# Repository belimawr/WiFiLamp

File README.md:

WiFi Lamp
=========

This is a simple project that uses a ESP8266-01 and a 2-coil latching relay
to control a lamp (or any other load) over WiFi using a simple web page.

TODO
----
 - Add the schematic
 - Create a nice PCB
 - Improve the web page

Licence
-------
**GPLV3**

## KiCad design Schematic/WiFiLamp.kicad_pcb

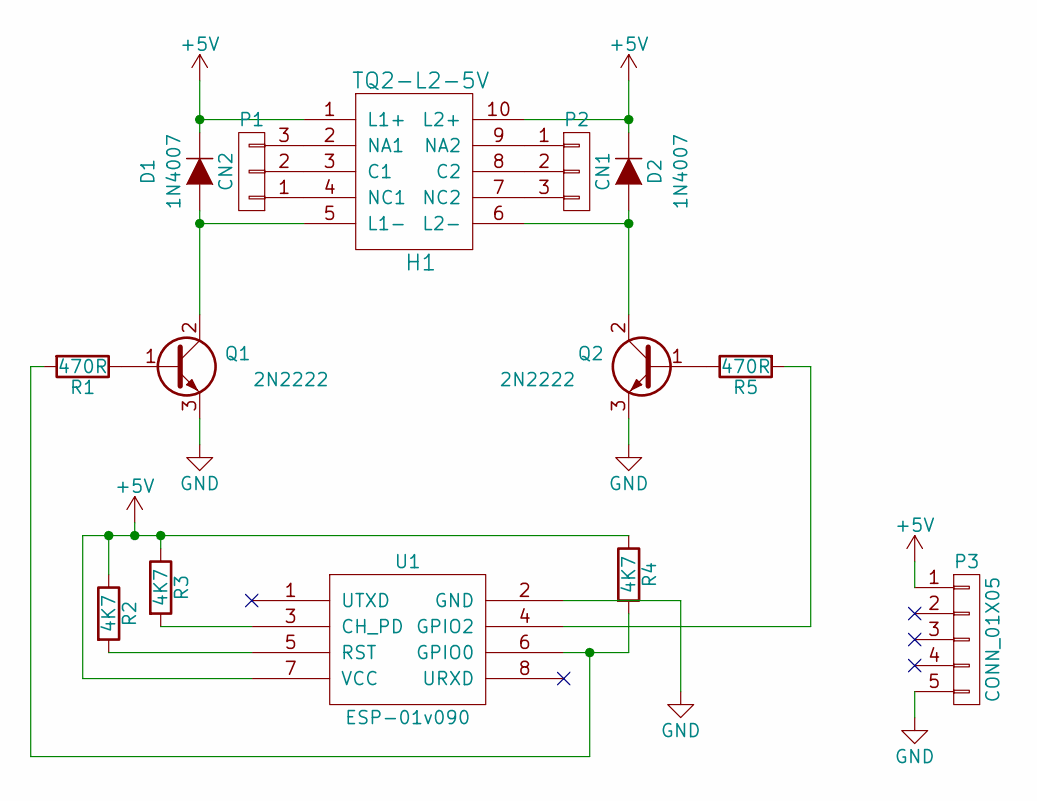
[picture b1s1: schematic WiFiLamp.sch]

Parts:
D1, D2: 1N4007; D_DO-41_SOD81_P10.16mm_Horizontal
H1: TQ2-L2-5V; ATQ229
P1: CN2; Pin_Header_Straight_1x03_Pitch2.54mm
P2: CN1; Pin_Header_Straight_1x03_Pitch2.54mm
P3: CONN_01X05; Pin_Header_Straight_1x05_Pitch2.54mm
Q1, Q2: 2N2222; TO-92_Inline_Narrow_Oval
R1, R5: 470R; R_Axial_DIN0207_L6.3mm_D2.5mm_P10.16mm_Horizontal
R2, R3, R4: 4K7; R_Axial_DIN0207_L6.3mm_D2.5mm_P10.16mm_Horizontal
U1: ESP-01v090; ESP-01

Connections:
+5V: D1.1 (K), D2.1 (K), H1.1 (L1+), H1.10 (L2+), P3.1, R2.1, R3.1, R4.1, U1.7 (VCC)
GND: P3.5, Q1.3 (E), Q2.3 (E), U1.2 (GND)
unnamed: D1.2 (A), H1.5 (L1-), Q1.2 (C)
unnamed: D2.2 (A), H1.6 (L2-), Q2.2 (C)
unnamed: H1.2 (NA1), P1.3
unnamed: H1.3 (C1), P1.2
unnamed: H1.4 (NC1), P1.1
unnamed: H1.7 (NC2), P2.3
unnamed: H1.8 (C2), P2.2
unnamed: H1.9 (NA2), P2.1
unnamed: Q1.1 (B), R1.1
unnamed: Q2.1 (B), R5.1
unnamed: R1.2, R4.2, U1.6 (GPIO0)
unnamed: R2.2, U1.5 (RST)
unnamed: R3.2, U1.3 (CH_PD)
unnamed: R5.2, U1.4 (GPIO2)

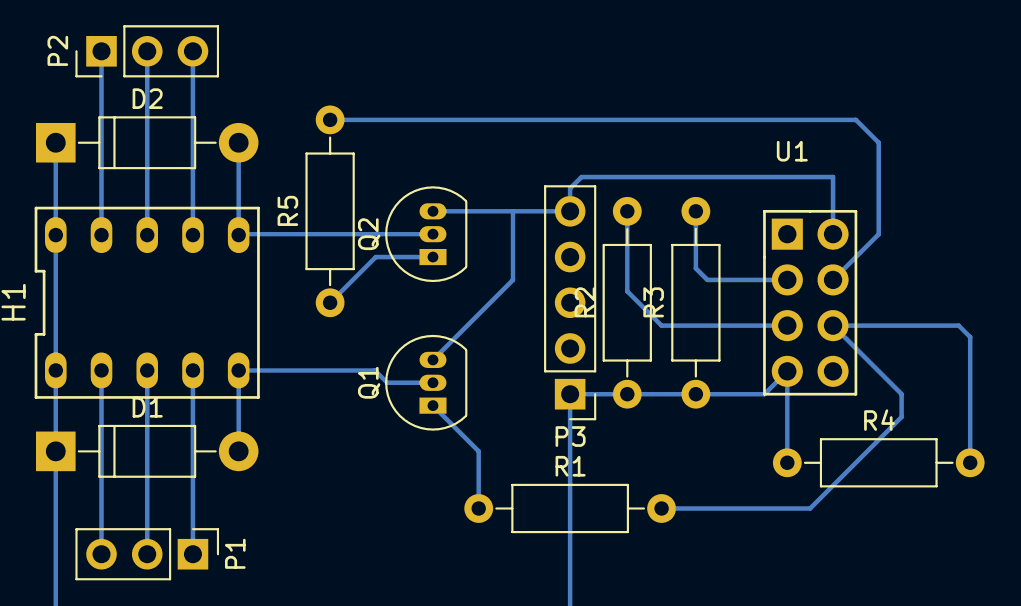
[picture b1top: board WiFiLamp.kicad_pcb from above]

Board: 2 copper layers, 14 parts (0 on the bottom side), 16 nets.

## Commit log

2017-01-08 Initial commit. Adding Readme and license
2017-01-08 Adding ESP8266 source code
2017-02-19 Adding schematic
2017-02-19 smaller ESP8266-01
2017-02-19 removing submodules
2017-02-19 addinf kicad libraries
